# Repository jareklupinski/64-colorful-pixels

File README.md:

# 64-colorful-pixels
A cheap array of red, green, and blue dots

Work in progress: how to design the least expensive board that can drive those inexpensive 8x8 RGB LED arrays, with chaining and gif playback capability.

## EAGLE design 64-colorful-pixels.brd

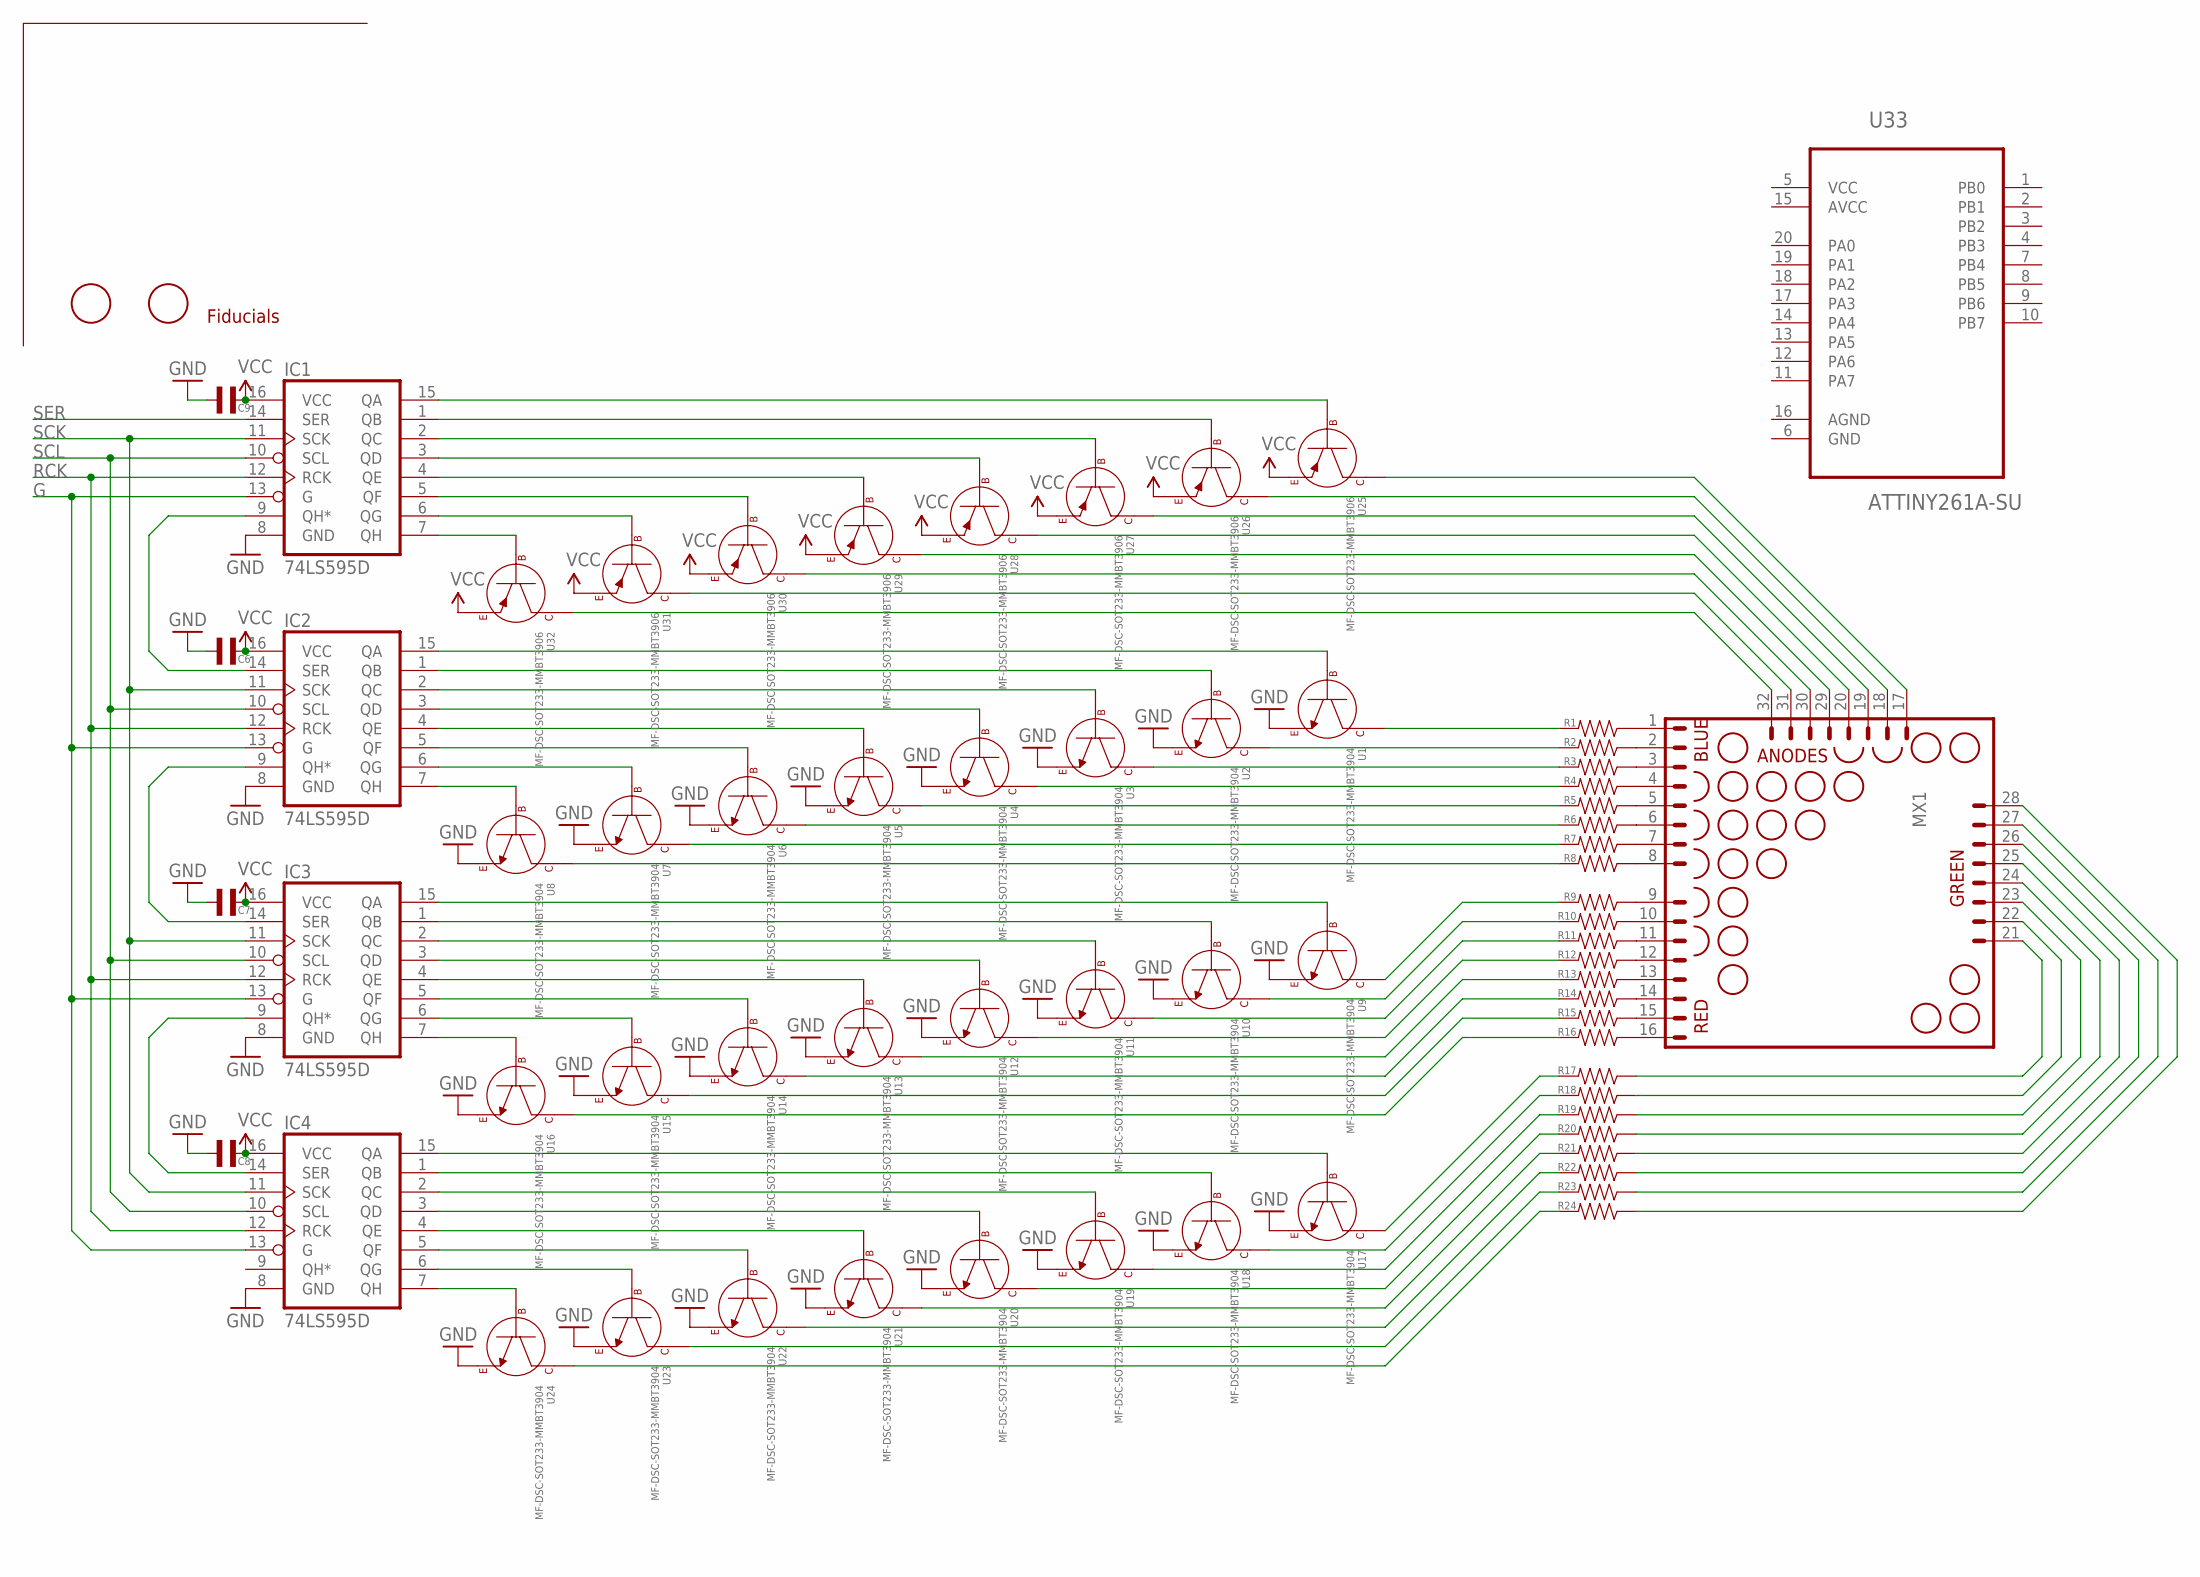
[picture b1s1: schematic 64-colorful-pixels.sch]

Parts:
C6, C7, C8, C9: CAPACITOR_NP_0402; C0402
IC1, IC2, IC3, IC4: 74LS595D; SO16
MX1: MATRIX_8X8_TRICOLOR_ANODE_ROW; MATRIX_60MM_32PIN
Q1, Q2: FIDUCIAL; FIDUCIAL_1MM
R1, R2, R3, R4, R5, R6, R7, R8, R9, R10, R11, R12, R13, R14, R15, R16, R17, R18, R19, R20, R21, R22, R23, R24: RESISTOR_0402; R0402
U1, U2, U3, U4, U5, U6, U7, U8, U9, U10, U11, U12, U13, U14, U15, U16, U17, U18, U19, U20, U21, U22, U23, U24: MF-DSC-SOT233-MMBT3904; SOT-23-3
U25, U26, U27, U28, U29, U30, U31, U32: MF-DSC-SOT233-MMBT3906; SOT-23-3
U33: ATTINY261A-SU; SOIC127P1032X265-20N

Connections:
AVCC: U33.15 (AVCC)
G: IC1.13 (G), IC2.13 (G), IC3.13 (G), IC4.13 (G)
GND: C6.P$1, C7.P$1, C8.P$1, C9.P$1, IC1.8 (GND), IC2.8 (GND), IC3.8 (GND), IC4.8 (GND), U1.P$2 (EMITTER), U2.P$2 (EMITTER), U3.P$2 (EMITTER), U4.P$2 (EMITTER), U5.P$2 (EMITTER), U6.P$2 (EMITTER), U7.P$2 (EMITTER), U8.P$2 (EMITTER), U9.P$2 (EMITTER), U10.P$2 (EMITTER), U11.P$2 (EMITTER), U12.P$2 (EMITTER), U13.P$2 (EMITTER), U14.P$2 (EMITTER), U15.P$2 (EMITTER), U16.P$2 (EMITTER), U17.P$2 (EMITTER), U18.P$2 (EMITTER), U19.P$2 (EMITTER), U20.P$2 (EMITTER), U21.P$2 (EMITTER), U22.P$2 (EMITTER), U23.P$2 (EMITTER), U24.P$2 (EMITTER)
unnamed: MX1.17, U25.P$3 (COLLECTOR)
unnamed: MX1.18, U26.P$3 (COLLECTOR)
unnamed: MX1.19, U27.P$3 (COLLECTOR)
unnamed: MX1.1, R1.P$1
unnamed: R1.P$2, U1.P$3 (COLLECTOR)
unnamed: MX1.20, U28.P$3 (COLLECTOR)
unnamed: MX1.29, U29.P$3 (COLLECTOR)
unnamed: MX1.2, R2.P$1
unnamed: MX1.3, R3.P$1
unnamed: MX1.30, U30.P$3 (COLLECTOR)
unnamed: MX1.4, R4.P$1
unnamed: MX1.31, U31.P$3 (COLLECTOR)
unnamed: MX1.5, R5.P$1
unnamed: MX1.6, R6.P$1
unnamed: MX1.7, R7.P$1
unnamed: MX1.8, R8.P$1
unnamed: R2.P$2, U2.P$3 (COLLECTOR)
unnamed: R3.P$2, U3.P$3 (COLLECTOR)
unnamed: R4.P$2, U4.P$3 (COLLECTOR)
unnamed: R5.P$2, U5.P$3 (COLLECTOR)
unnamed: R6.P$2, U6.P$3 (COLLECTOR)
unnamed: R7.P$2, U7.P$3 (COLLECTOR)
unnamed: R8.P$2, U8.P$3 (COLLECTOR)
unnamed: MX1.21, R17.P$1
unnamed: MX1.22, R18.P$1
unnamed: MX1.23, R19.P$1
unnamed: MX1.24, R20.P$1
unnamed: MX1.25, R21.P$1
unnamed: MX1.26, R22.P$1
unnamed: MX1.27, R23.P$1
unnamed: MX1.28, R24.P$1
unnamed: MX1.32, U32.P$3 (COLLECTOR)
unnamed: IC1.15 (QA), U25.P$1 (BASE)
unnamed: IC1.1 (QB), U26.P$1 (BASE)
unnamed: IC1.2 (QC), U27.P$1 (BASE)
unnamed: IC1.3 (QD), U28.P$1 (BASE)
unnamed: IC1.4 (QE), U29.P$1 (BASE)
unnamed: IC1.5 (QF), U30.P$1 (BASE)
unnamed: IC1.6 (QG), U31.P$1 (BASE)
unnamed: IC1.7 (QH), U32.P$1 (BASE)
unnamed: IC2.15 (QA), U1.P$1 (BASE)
unnamed: IC2.1 (QB), U2.P$1 (BASE)
unnamed: IC2.2 (QC), U3.P$1 (BASE)
unnamed: IC2.3 (QD), U4.P$1 (BASE)
unnamed: IC2.4 (QE), U5.P$1 (BASE)
unnamed: IC2.5 (QF), U6.P$1 (BASE)
unnamed: IC2.6 (QG), U7.P$1 (BASE)
unnamed: IC2.7 (QH), U8.P$1 (BASE)
unnamed: IC3.15 (QA), U9.P$1 (BASE)
unnamed: IC3.1 (QB), U10.P$1 (BASE)
unnamed: IC3.2 (QC), U11.P$1 (BASE)
unnamed: IC3.3 (QD), U12.P$1 (BASE)
unnamed: IC3.4 (QE), U13.P$1 (BASE)
unnamed: IC3.5 (QF), U14.P$1 (BASE)
unnamed: IC3.6 (QG), U15.P$1 (BASE)
unnamed: IC3.7 (QH), U16.P$1 (BASE)
unnamed: IC4.15 (QA), U17.P$1 (BASE)
unnamed: IC4.1 (QB), U18.P$1 (BASE)
unnamed: IC4.2 (QC), U19.P$1 (BASE)
unnamed: IC4.3 (QD), U20.P$1 (BASE)
unnamed: IC4.4 (QE), U21.P$1 (BASE)
unnamed: IC4.5 (QF), U22.P$1 (BASE)
unnamed: IC4.6 (QG), U23.P$1 (BASE)
unnamed: IC4.7 (QH), U24.P$1 (BASE)
unnamed: MX1.9, R9.P$1
unnamed: MX1.10, R10.P$1
unnamed: MX1.11, R11.P$1
unnamed: MX1.12, R12.P$1
unnamed: MX1.13, R13.P$1
unnamed: R9.P$2, U9.P$3 (COLLECTOR)
unnamed: MX1.14, R14.P$1
unnamed: MX1.15, R15.P$1
unnamed: MX1.16, R16.P$1
unnamed: R10.P$2, U10.P$3 (COLLECTOR)
unnamed: R11.P$2, U11.P$3 (COLLECTOR)
unnamed: R12.P$2, U12.P$3 (COLLECTOR)
unnamed: R13.P$2, U13.P$3 (COLLECTOR)
unnamed: R14.P$2, U14.P$3 (COLLECTOR)
unnamed: R15.P$2, U15.P$3 (COLLECTOR)
unnamed: R16.P$2, U16.P$3 (COLLECTOR)
unnamed: R17.P$2, U17.P$3 (COLLECTOR)
unnamed: R18.P$2, U18.P$3 (COLLECTOR)
unnamed: R19.P$2, U19.P$3 (COLLECTOR)
unnamed: R20.P$2, U20.P$3 (COLLECTOR)
unnamed: R21.P$2, U21.P$3 (COLLECTOR)
unnamed: R22.P$2, U22.P$3 (COLLECTOR)
unnamed: R23.P$2, U23.P$3 (COLLECTOR)
unnamed: R24.P$2, U24.P$3 (COLLECTOR)
unnamed: IC1.9 (QH*), IC2.14 (SER)
unnamed: IC2.9 (QH*), IC3.14 (SER)
unnamed: IC3.9 (QH*), IC4.14 (SER)
RCK: IC1.12 (RCK), IC2.12 (RCK), IC3.12 (RCK), IC4.12 (RCK)
SCK: IC1.11 (SCK), IC2.11 (SCK), IC3.11 (SCK), IC4.11 (SCK)
SCL: IC1.10 (SCL), IC2.10 (SCL), IC3.10 (SCL), IC4.10 (SCL)
SER: IC1.14 (SER)
VCC: C6.P$2, C7.P$2, C8.P$2, C9.P$2, IC1.16 (VCC), IC2.16 (VCC), IC3.16 (VCC), IC4.16 (VCC), U25.P$2 (EMITTER), U26.P$2 (EMITTER), U27.P$2 (EMITTER), U28.P$2 (EMITTER), U29.P$2 (EMITTER), U30.P$2 (EMITTER), U31.P$2 (EMITTER), U32.P$2 (EMITTER), U33.5 (VCC)

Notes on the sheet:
Fiducials

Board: 2 copper layers, 68 parts (0 on the bottom side), 97 nets, no tracks yet.

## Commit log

2018-07-06 work in progress

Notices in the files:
parts and their libraries:
matrix: Designs by Ed Halley.  Released into the Creative Commons, with Attribution-Only, Share-Alike.
SparkFun-DigitalIC: Licensing: Creative Commons ShareAlike 4.0 International - https://creativecommons.org/licenses/by-sa/4.0
